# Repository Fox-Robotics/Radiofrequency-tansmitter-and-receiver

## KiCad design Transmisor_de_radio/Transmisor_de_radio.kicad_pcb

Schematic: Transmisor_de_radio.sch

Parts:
C1: 100uF; C_Elec_6.3x7.7
C2, C4, C6: 100uF; CP_Elec_6.3x5.4
C3, C5, C9: 0.1uF; C_0805_2012Metric_Pad1.18x1.45mm_HandSolder
C7, C8: 22pF; C_0805_2012Metric_Pad1.18x1.45mm_HandSolder
D1: LED; LED_0805_2012Metric
H1, H2, H3, H4: MountingHole; MountingHole_2.7mm
J1: Battery; PinHeader_1x02_P2.54mm_Vertical
J3: Conn_01x06_Male; PinSocket_1x06_P2.54mm_Vertical
J6: Conn_01x08_Male; PinSocket_2x04_P2.54mm_Vertical_SMD
R1: 200; R_0805_2012Metric_Pad1.20x1.40mm_HandSolder
R2: 10k; R_0805_2012Metric_Pad1.20x1.40mm_HandSolder
SW1, SW4: SW_SPDT; SW_100SP1T1B4M2QE
SW2: SW_Push; PinSocket_1x03_P2.54mm_Vertical
SW3: SW_SPDT; PinSocket_1x03_P2.54mm_Vertical
U1: ATmega328-PU; DIP-28_W7.62mm
U2: AMS1117-3.3; SOT-223-3_TabPin2
U3: AMS1117-5.0; SOT-223-3_TabPin2
U4: JOYSTICK_L; XDCR_COM-09032; PARTREV N/A
U5: JOYSTICK_R; XDCR_COM-09032; PARTREV N/A
Y1: Crystal; Crystal_SMD_0603-2Pin_6.0x3.5mm_HandSoldering

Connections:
3.3v: C3.1, C4.1, J6.8, U2.2 (VO)
CE: J6.5, U1.13 (PD7)
CSN: J6.6, U1.14 (PB0)
DTR: C5.2, J3.6
GND: C1.2, C2.2, C3.2, C4.2, C6.2, C7.1, C8.1, C9.2, J1.2, J3.1, J6.7, R1.1, SW1.3 (C), SW2.2, SW4.3 (C), U1.8 (GND), U1.22 (GND), U2.1 (GND), U3.1 (GND), U4.H3 (H-), U4.V3 (V-), U5.H3 (H-), U5.V3 (V-)
MISO: J6.1, U1.18 (PB4)
MOSI: J6.4, U1.17 (PB3)
unnamed: C2.1, SW3.3 (C), U3.3 (VI)
unnamed: C5.1, R2.2, SW2.1, U1.1 (~RESET~/PC6)
unnamed: C7.2, U1.9 (XTAL1/PB6), Y1.1
unnamed: C8.2, U1.10 (XTAL2/PB7), Y1.2
unnamed: D1.1 (K), R1.2
unnamed: J1.1, SW3.2 (B)
unnamed: U4.S1 (SHIELD), U4.S2 (SHIELD), U4.S3 (SHIELD), U4.S4 (SHIELD)
unnamed: U5.S1 (SHIELD), U5.S2 (SHIELD), U5.S3 (SHIELD), U5.S4 (SHIELD)
Rx: J3.4, U1.2 (PD0)
SCK: D1.2 (A), J6.3, U1.19 (PB5)
Toogle_L: SW4.2 (B), U1.4 (PD2)
Toogle_R: SW1.2 (B), U1.6 (PD4)
Tx: J3.5, U1.3 (PD1)
VCC: C1.1, C6.1, C9.1, J3.3, R2.1, SW1.1 (A), SW4.1 (A), U1.7 (VCC), U1.20 (AVCC), U1.21 (AREF), U2.3 (VI), U3.2 (VO), U4.H1 (H+), U4.V1 (V+), U5.H1 (H+), U5.V1 (V+)
Xout_L: U1.23 (PC0), U4.V2 (V)
Xout_R: U1.25 (PC2), U5.V2 (V)
Yout_L: U1.24 (PC1), U4.H2 (H)
Yout_R: U1.26 (PC3), U5.H2 (H)

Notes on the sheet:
ATmega328 PU
Power 5v
Joysticks
UART
NRF24
Power 3.3v
Toggle switches
Fox robotics
Radio transmitter V2
Designed by: Luis Adrian Cabrera Muñoz

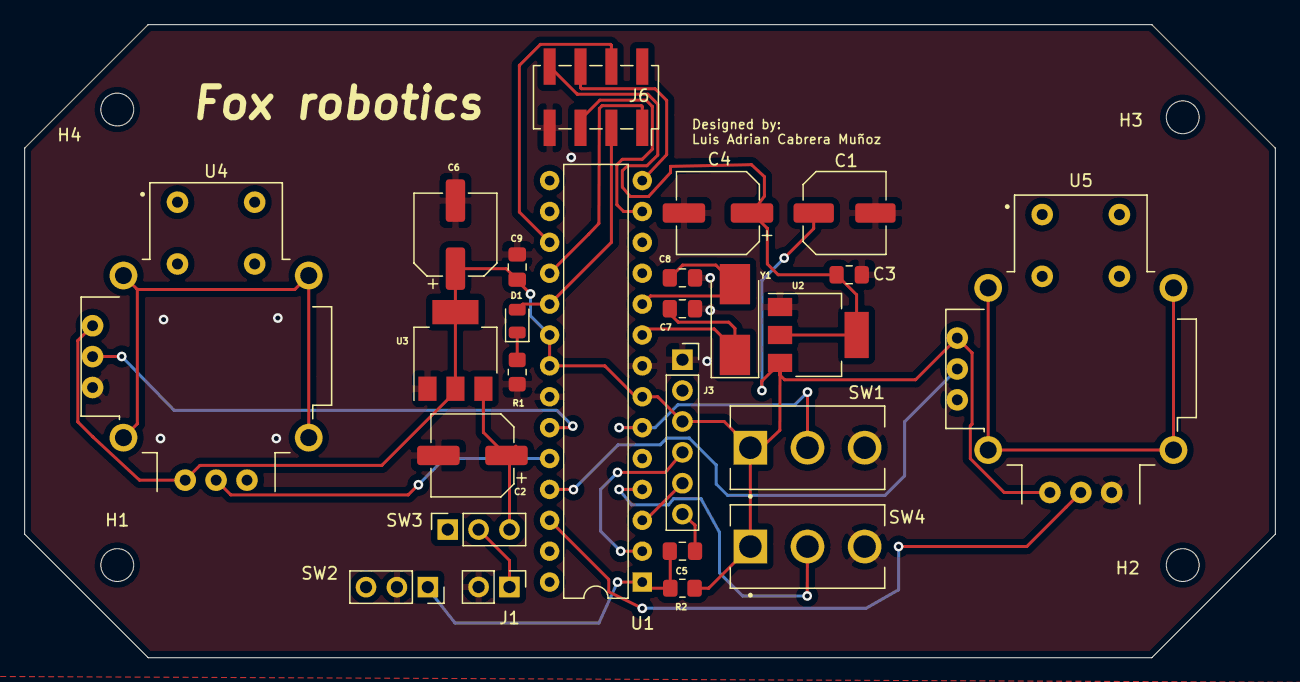
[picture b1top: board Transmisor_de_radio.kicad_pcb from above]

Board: 2 copper layers, 102.9 x 52.1 mm, 29 parts (0 on the bottom side), 25 nets.
